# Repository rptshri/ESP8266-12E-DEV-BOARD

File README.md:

# ESP8266-12E-DEV-BOARD
THIS IS A ESP8266-12E DEV BOARD EAGLE SCHEMATICS AND BOARD.

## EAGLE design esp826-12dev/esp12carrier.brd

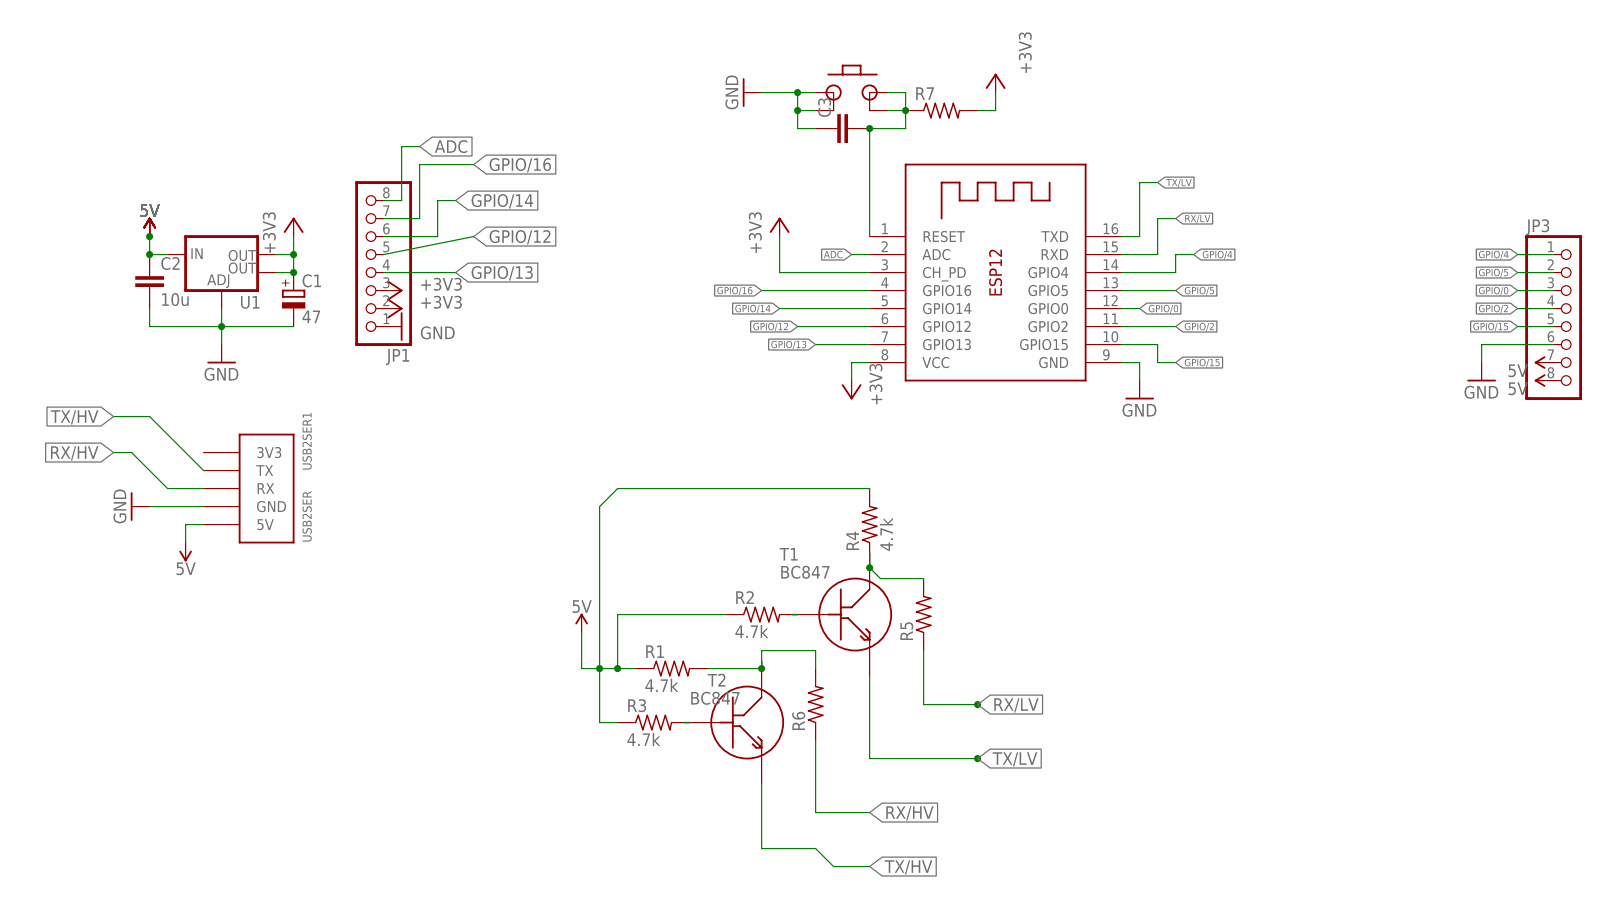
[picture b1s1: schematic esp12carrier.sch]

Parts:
C1: 47; 150CLZ-0810
C2: 10u; C0805
C3: C-EUC0805; C0805
JP1, JP3: PINHD-1X8; 1X08
PB1: TACTSW
R1, R2, R3, R4: 4.7k; M0805
R5, R6, R7: R-US_M0805; M0805
T1, T2: BC847
U1: V_REG_LM1117SOT223; SOT223
USB2SER1: USB2SER
X2: ESP-12

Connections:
3V3: USB2SER1.P$1 (3V3)
5V: C2.1, JP3.7, JP3.8, R1.1, R2.1, R3.1, R4.2, U1.3 (IN), USB2SER1.P$5 (5V)
+3V3: C1.+, JP1.2, JP1.3, R7.2, U1.2 (OUT), U1.4 (OUT), X2.3 (CH_PD), X2.8 (VCC)
ADC: JP1.8, X2.2 (ADC)
GND: C1.-, C2.2, C3.1, JP1.1, JP3.6, PB1.P$1, PB1.P$2, U1.1 (ADJ), USB2SER1.P$4 (GND), X2.9 (GND)
GPIO/0: JP3.3, X2.12 (GPIO0)
GPIO/2: JP3.4, X2.11 (GPIO2)
GPIO/4: JP3.1, X2.14 (GPIO4)
GPIO/5: JP3.2, X2.13 (GPIO5)
GPIO/12: JP1.5, X2.6 (GPIO12)
GPIO/13: JP1.4, X2.7 (GPIO13)
GPIO/14: JP1.6, X2.5 (GPIO14)
GPIO/15: JP3.5, X2.10 (GPIO15)
GPIO/16: JP1.7, X2.4 (GPIO16)
unnamed: R2.2, T1.P$2 (B)
unnamed: R1.2, R6.2, T2.P$1 (C)
unnamed: R3.2, T2.P$2 (B)
unnamed: R4.1, R5.2, T1.P$1 (C)
unnamed: C3.2, PB1.P$3, PB1.P$4, R7.1, X2.1 (RESET)
RX/HV: R6.1, USB2SER1.P$3 (RX)
RX/LV: R5.1, X2.15 (RXD)
TX/HV: T2.P$3 (E), USB2SER1.P$2 (TX)
TX/LV: T1.P$3 (E), X2.16 (TXD)

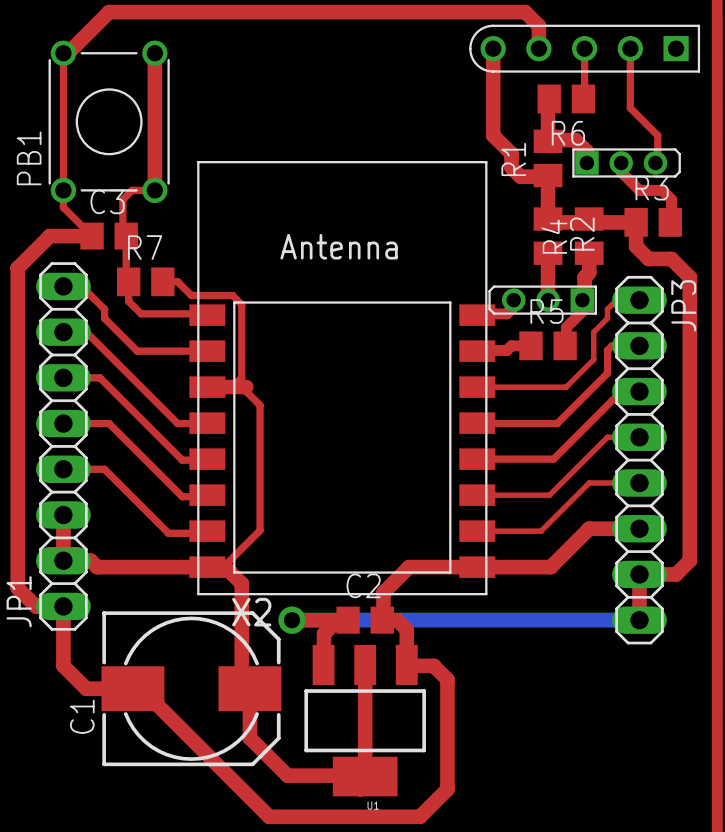
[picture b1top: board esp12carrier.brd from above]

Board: 2 copper layers, 18 parts (0 on the bottom side), 22 nets.

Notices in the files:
parts and their libraries:
SparkFun-IC-Power: Licensing: Creative Commons ShareAlike 4.0 International - https://creativecommons.org/licenses/by-sa/4.0
